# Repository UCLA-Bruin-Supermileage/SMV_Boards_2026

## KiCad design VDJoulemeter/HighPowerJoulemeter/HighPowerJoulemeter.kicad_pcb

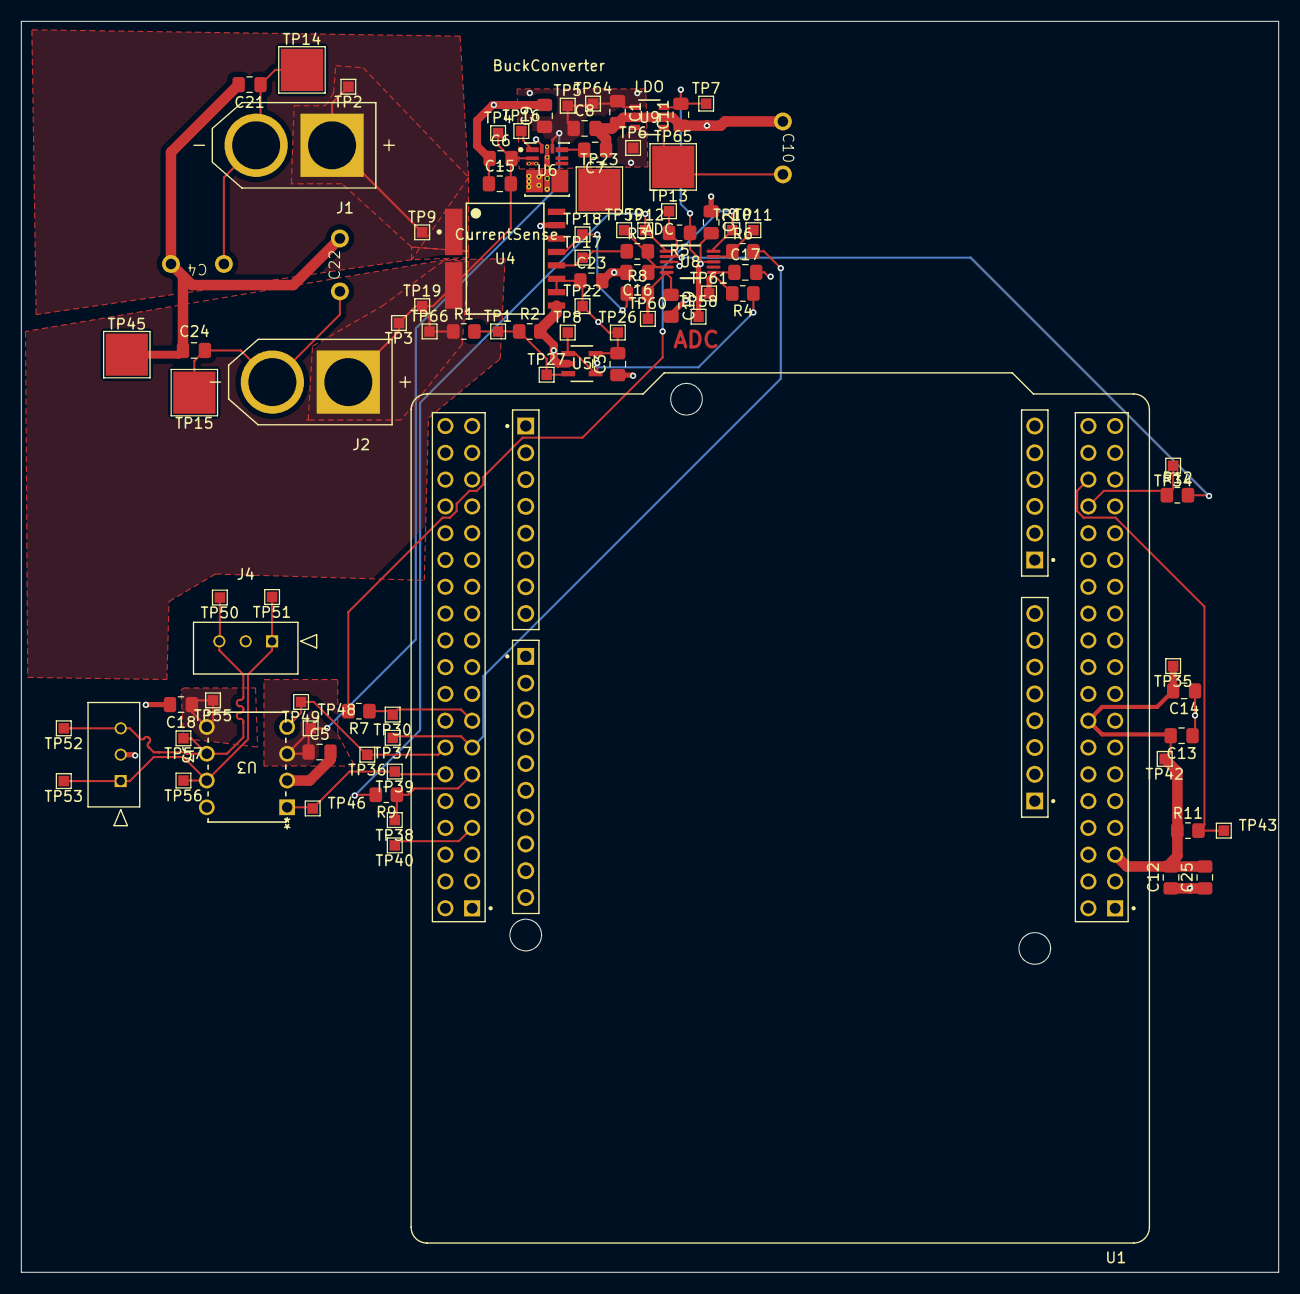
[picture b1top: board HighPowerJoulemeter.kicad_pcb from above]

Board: 4 copper layers, 119.2 x 118.6 mm, 97 parts (0 on the bottom side), 30 nets.

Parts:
C1, C2, C3, C5, C12, C13, C14, C15, C16, C17, C18, C19, C23: 0.1uF; C_0805_2012Metric_Pad1.18x1.45mm_HandSolder
C4, C22: 470uF, 63V; Big_Chunky_Cap
C6, C11: 2.2uF; C_0805_2012Metric_Pad1.18x1.45mm_HandSolder
C7: 1uF; C_0805_2012Metric_Pad1.18x1.45mm_HandSolder
C8, C9: 22uF; C_0805_2012Metric_Pad1.18x1.45mm_HandSolder
C10: 470pF; Big_Chunky_Cap
C21, C24, C25: 10uF; C_0805_2012Metric_Pad1.18x1.45mm_HandSolder
J1, J2: XT60-M; AMASS_XT60-M
J3, J4: 22035035; 3pin_CON_22035035_MOL
R1: 500kΩ; R_0805_2012Metric_Pad1.20x1.40mm_HandSolder
R2: 20kΩ; R_0805_2012Metric_Pad1.20x1.40mm_HandSolder
R3, R4, R8: 500Ω; R_0805_2012Metric_Pad1.20x1.40mm_HandSolder
R5: 4k7; R_0805_2012Metric_Pad1.20x1.40mm_HandSolder
R6, R7, R9, R12: 50Ω; R_0805_2012Metric_Pad1.20x1.40mm_HandSolder
R11: 0Ω; R_0805_2012Metric_Pad1.20x1.40mm_HandSolder
TP1, TP2, TP3, TP4, TP5, TP6, TP7, TP8, TP9, TP10, TP11, TP12, TP13, TP16, TP17, TP18, TP19, TP22, TP26, TP27, TP30, TP34, TP35, TP36, TP37, TP38, TP39, TP40, TP42, TP43, TP46, TP48, TP49, TP50, TP51, TP52, TP53, TP55, TP56, TP57, TP58, TP59, TP60, TP61, TP64, TP66: TestPoint; TestPoint_Pad_1.0x1.0mm
TP14, TP15, TP23, TP45, TP65: TestPoint; TestPoint_Pad_4.0x4.0mm
U1: MODULE_NUCLEO-F446RE
U3: MCP2562; PDIP8_300MC_MCH
U4: TMCS1126B6AQDVGRQ1; DVG0010A-MFG
U5: MCP6286T-E/OT; SOT-23-5_MC_MCH
U6: PTPSM365R6V5RDNR; RDN0011A-MFG
U8: ADS1118QDGSRQ1; DGS0010A_N
U9: MIC5219-3.3YM5-TR; SOT-23-5_M5_MCH

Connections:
48V_IN: J1.P (POS), TP2.1, TP9.1, U4.1 (IN+)
48V_OUT: C6.2, C15.2, J2.P (POS), R1.1, TP3.1, TP4.1, TP19.1, TP66.1, U4.2 (IN-), U6.2 (EN), U6.3 (VIN)
+3.3V: C2.2, C3.2, C11.2, C12.2, C13.2, C14.2, C18.1, C23.1, C25.2, R5.1, R11.1, TP7.1, TP22.1, TP26.1, TP35.1, TP40.1, TP42.1, TP55.1, TP58.1, U1.5 (VDD), U1.16 (+3V3), U1.45 (AVDD), U3.5 (V_IO), U4.4 (VS), U4.5 (VOC), U5.5 (VDD), U8.8 (VDD), U9.5 (OUT)
+5V: C1.1, C5.1, C8.1, C9.1, TP5.1, TP6.1, TP48.1, TP64.1, U3.3 (VDD), U6.4 (VOUT), U6.9 (BIAS), U9.1 (IN), U9.3 (EN)
/CAN_N: J3.3, J4.3, TP50.1, TP52.1, TP57.1, U3.6 (CANL)
/CAN_P: J3.1, J4.1, TP51.1, TP53.1, TP56.1, U3.7 (CANH)
/I_Sense: R3.1, TP17.1, U4.6 (VOUT)
/SCK: R9.2, TP12.1, U8.1 (SCLK)
/STM32ChipSelectSignal: R5.2, R12.2, TP13.1, U8.2 (CS_N)
/STM_CAN_RX_PIN: TP36.1, TP49.1, U1.52 (PA11), U3.4 (RXD)
/STM_CAN_TX_PIN: TP39.1, TP46.1, U1.50 (PA12), U3.1 (TXD)
/STM_MISO: R6.2, TP37.1, U1.51 (PA6)
/STM_MOSI: R7.2, TP10.1, U8.10 (DIN)
/V_Ref: R8.1, TP18.1, U4.7 (VREF)
/V_Sense: R4.1, TP8.1, U5.1 (VOUT), U5.4 (VIN-)
/VoltageDividerOut: R1.2, R2.1, TP1.1, TP27.1, U5.3 (VIN+)
GND: C1.2, C2.1, C3.1, C4.3, C5.2, C6.1, C7.1, C8.2, C9.2, C10.4, C11.1, C12.1, C13.1, C14.1, C15.1, C16.2, C17.2, C18.2, C19.2, C21.2, C22.3, C23.2, C24.2, C25.1, J3.2, J4.2, R2.2, TP45.1, U1.8 (GND), U1.19 (GND), U1.20 (GND), U1.22 (GND), U1.47 (GND), U1.58 (GND), U1.70 (AGND), U3.2 (VSS), U3.8 (STBY), U4.3 (*OC), U4.9 (GND), U5.2 (VSS), U6.10 (GND), U6.11 (MODE_SYNC), U8.3 (GND), U9.2 (GND)
unnamed: C4.4, C21.1, J1.N (NEG), TP14.1
unnamed: C22.4, C24.1, J2.N (NEG), TP15.1
unnamed: R12.1, TP34.1, U1.32 (PA4)
unnamed: R9.1, TP38.1, U1.49 (PA5)
unnamed: R7.1, TP30.1, U1.53 (PA7)
unnamed: R11.2, TP43.1, U1.34 (PB0)
unnamed: TP16.1, U6.1 (PGOOD)
unnamed: C7.2, TP23.1, U6.8 (VCC)
unnamed: C16.1, R3.2, TP59.1, U8.4 (AIN0)
unnamed: C19.1, R8.2, TP60.1, U8.5 (AIN1)
unnamed: C17.1, R4.2, TP61.1, U8.6 (AIN2)
unnamed: R6.1, TP11.1, U8.9 (DOUT_DRDY_N)
unnamed: C10.3, TP65.1, U9.4 (BYP)

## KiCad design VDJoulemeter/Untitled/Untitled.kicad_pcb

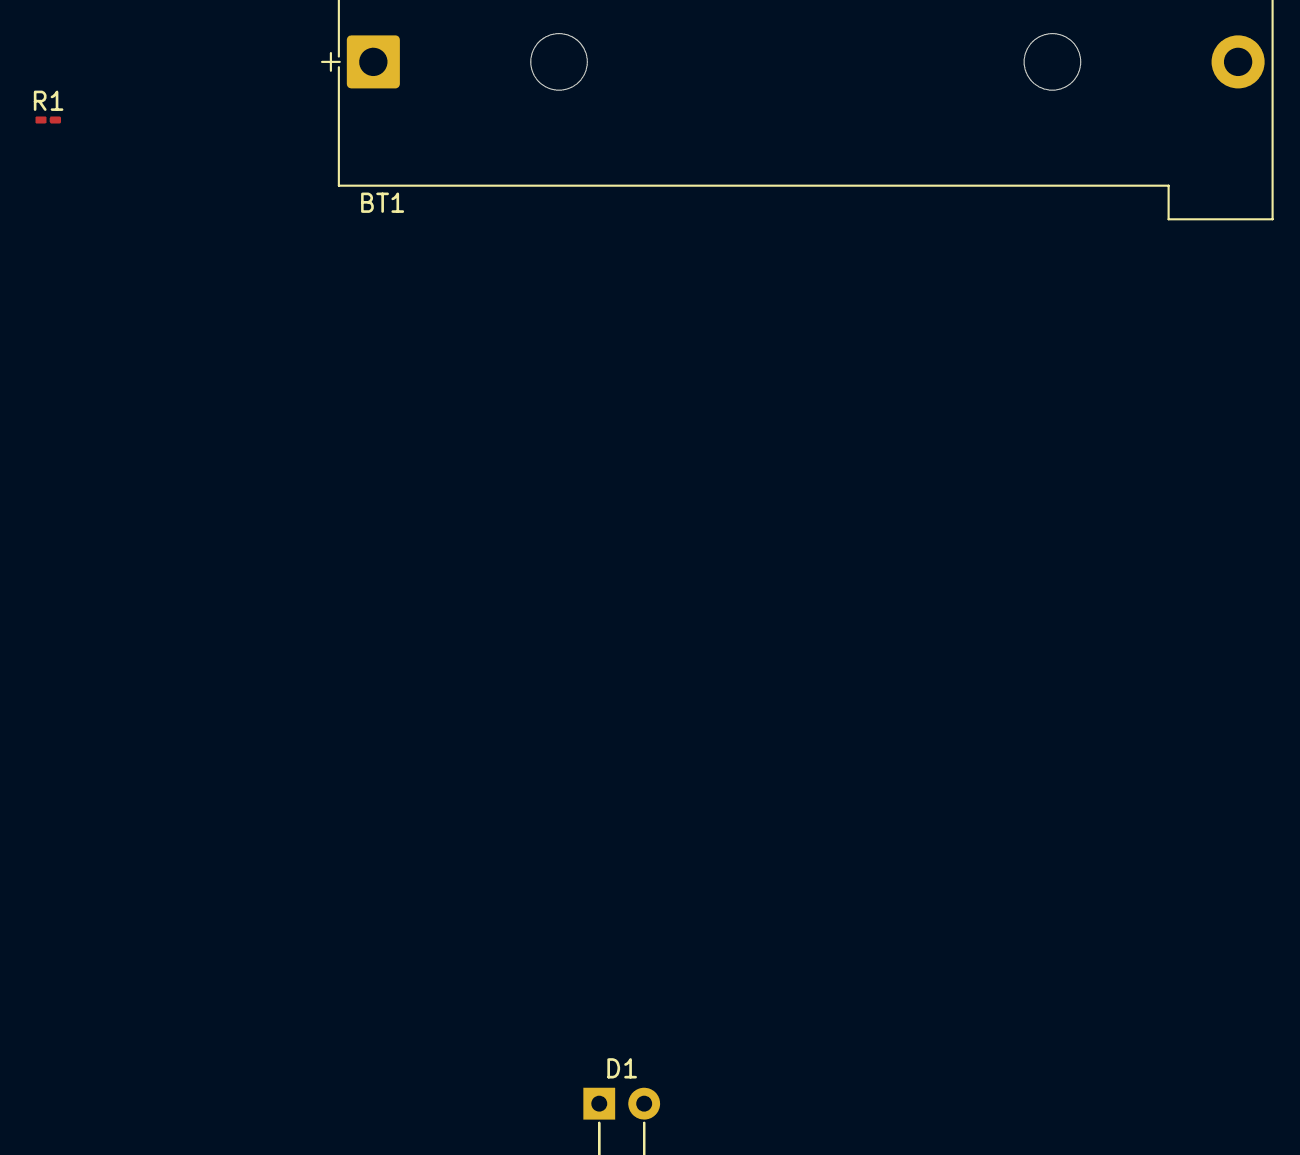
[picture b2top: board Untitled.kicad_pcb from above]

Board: 2 copper layers, 3 parts (0 on the bottom side), 3 nets, no tracks yet.

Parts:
BT1: 9V; BatteryHolder_Bulgin_BX0034_1xAAA
D1: LED; LED_D3.0mm_Horizontal_O6.35mm_Z2.0mm
R1: 200; R_0201_0603Metric_Pad0.64x0.40mm_HandSolder

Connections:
unnamed: BT1.1 (+), R1.2
unnamed: BT1.2 (-), D1.1 (K)
unnamed: D1.2 (A), R1.1
